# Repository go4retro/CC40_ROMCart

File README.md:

## Introduction

Store every ROM cartridge manufactured for the Texas Instruments Compact Computer 40 in a single unit with this mega cartridge. This CC-40 ROM cartridge replicates the functionality of the original application specific ROM cartridge option and also expands it up to 512KB.  Easy access DIP switches on the rear of the unit allow one to select which ROM bank is in use.

Discussion around the design can be reviewed on the AtariAge forum [discussion](https://atariage.com/forums/topic/255728-the-compact-computer-40-cc40/). 

### Main features

- Mimics original PCB location and size
- Up to 512kB ROM capacity
- Easy access to change accessed bank

### Technical Features

- ROM socket can be configured for FLASH or EPROM options
- Optional use of P25.2 and P25.3 signals on cartridge port to select ROM bank

## Purchase

This PCB can be purchased in the [RETRO Innovations Online Store](http://store.go4retro.com/ti-compact-computer-40-prototype-boards/).

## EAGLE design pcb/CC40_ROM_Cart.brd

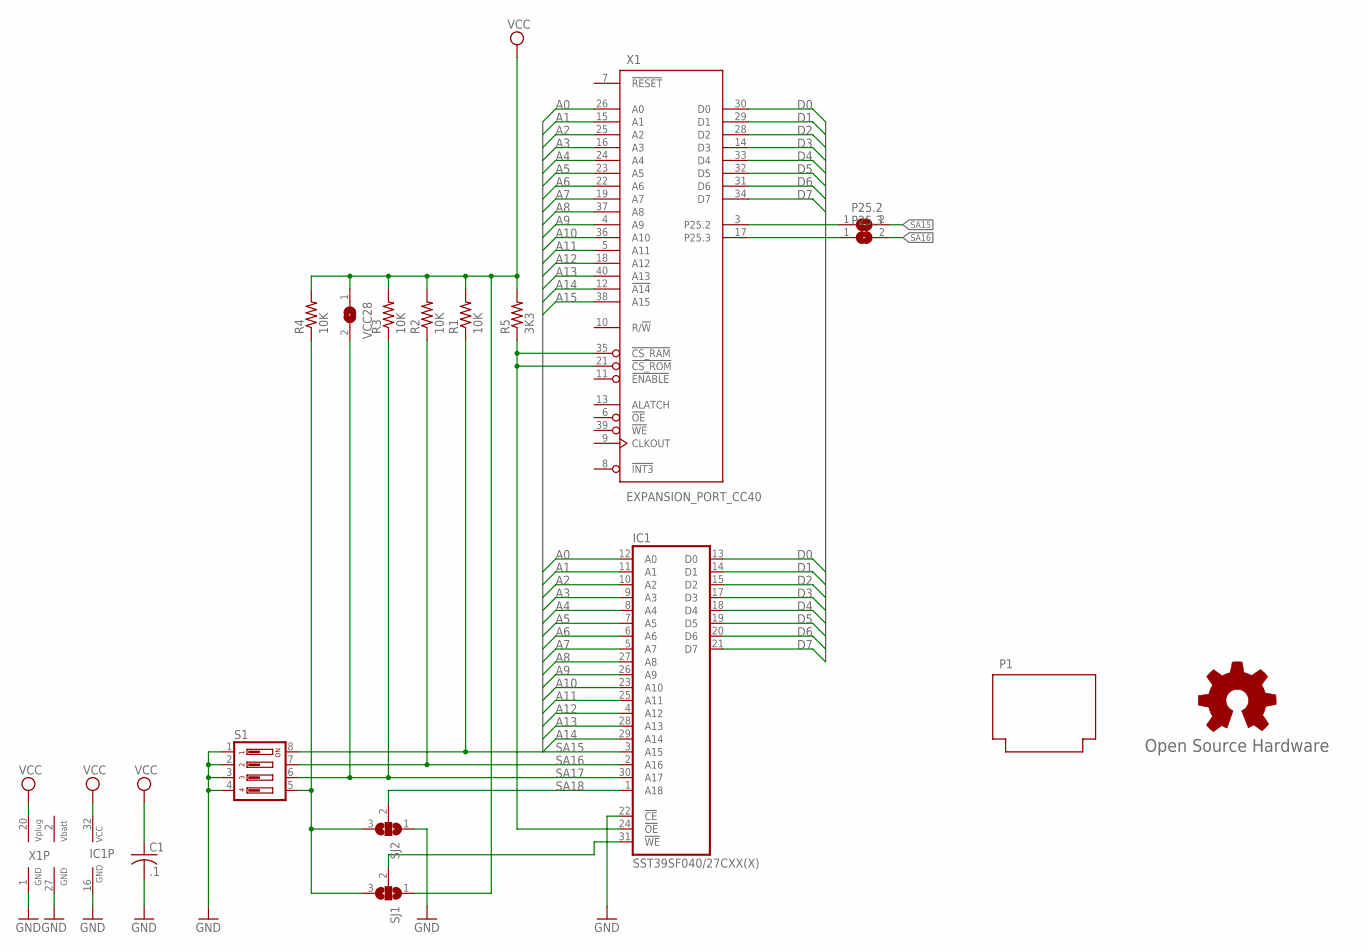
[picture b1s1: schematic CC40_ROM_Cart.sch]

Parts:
C1: .1; C025-025X050
GOLD_ORB_SM1: Open Source Hardware; OSHW_8MM
IC1: SST39SF040/27CXX(X); DIL32-RP
P1: CC40_CARTN; CC40_CART_NOHOLE
P25.2, P25.3: SJ
R1, R2, R3, R4: 10K; 0204/7
R5: 3K3; 0204/7
S1: DP04; DP-04
SJ1, SJ2: SJ2W; SJ_2
VCC28: SJ
X1: EXPANSION_PORT_CC40; MA20-2(.050)

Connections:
!CS: IC1.24 (!OE), R5.1, X1.21 (!CS_ROM), X1.35 (!CS_RAM)
!WE: IC1.31 (!WE), SJ1.2
A0: IC1.12 (A0), X1.26 (A0)
A1: IC1.11 (A1), X1.15 (A1)
A2: IC1.10 (A2), X1.25 (A2)
A3: IC1.9 (A3), X1.16 (A3)
A4: IC1.8 (A4), X1.24 (A4)
A5: IC1.7 (A5), X1.23 (A5)
A6: IC1.6 (A6), X1.22 (A6)
A7: IC1.5 (A7), X1.19 (A7)
A8: IC1.27 (A8), X1.37 (A8)
A9: IC1.26 (A9), X1.4 (A9)
A10: IC1.23 (A10), X1.36 (A10)
A11: IC1.25 (A11), X1.5 (A11)
A12: IC1.4 (A12), X1.18 (A12)
A13: IC1.28 (A13), X1.40 (A13)
A14: IC1.29 (A14), X1.12 (!A14)
A15: X1.38 (A15)
D0: IC1.13 (D0), X1.30 (D0)
D1: IC1.14 (D1), X1.29 (D1)
D2: IC1.15 (D2), X1.28 (D2)
D3: IC1.17 (D3), X1.14 (D3)
D4: IC1.18 (D4), X1.33 (D4)
D5: IC1.19 (D5), X1.32 (D5)
D6: IC1.20 (D6), X1.31 (D6)
D7: IC1.21 (D7), X1.34 (D7)
GND: C1.2, IC1.16 (GND), IC1.22 (!CE), S1.1, S1.2, S1.3, S1.4, SJ2.1, X1.1 (GND), X1.27 (GND)
SA15: IC1.3 (A15), P25.2.2, R1.1, S1.8
SA15': P25.2.1, X1.3 (P25.2)
SA16: IC1.2 (A16), P25.3.2, R2.1, S1.7
SA16': P25.3.1, X1.17 (P25.3)
SA17: IC1.30 (A17), R3.1, S1.6, VCC28.2
SA18: IC1.1 (A18), SJ2.2
SA18': R4.1, S1.5, SJ1.3, SJ2.3
VBATT: X1.2 (VBATT)
VCC: C1.1, IC1.32 (VCC), R1.2, R2.2, R3.2, R4.2, R5.2, SJ1.1, VCC28.1, X1.20 (VPLUG)

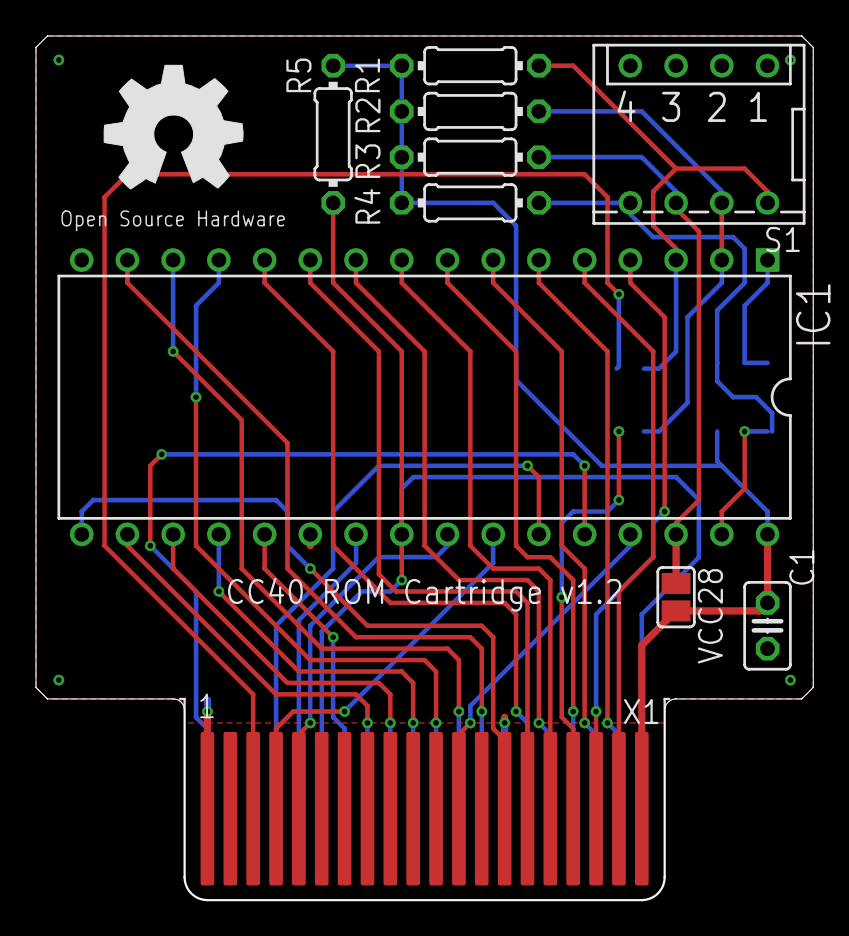
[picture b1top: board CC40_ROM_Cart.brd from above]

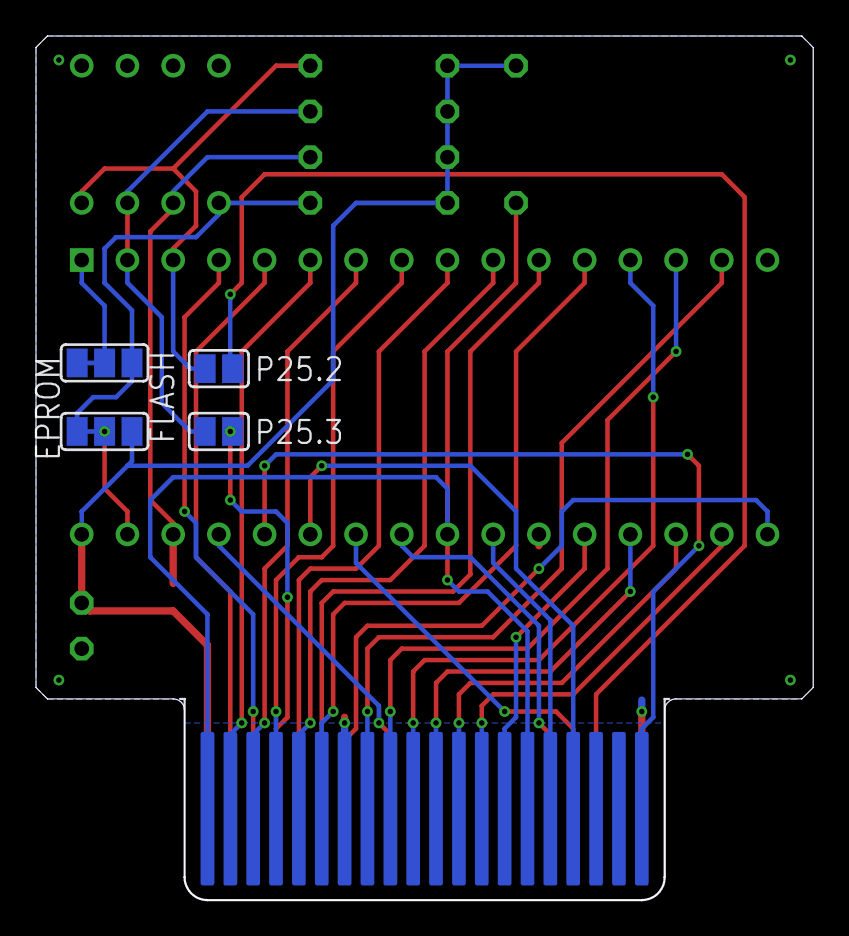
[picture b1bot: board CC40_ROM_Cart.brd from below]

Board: 2 copper layers, 43.2 x 48.0 mm, 16 parts (4 on the bottom side), 34 nets.

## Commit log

2024-07-14 Updated layouts and measurements

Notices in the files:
pcb/CC40_ROM_Cart.brd:
(c) 2017 RETRO Innovations
